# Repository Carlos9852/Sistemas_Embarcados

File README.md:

# Projeto_I
Projeto I da disciplina de Sistema Embarcados e Microcontroladores

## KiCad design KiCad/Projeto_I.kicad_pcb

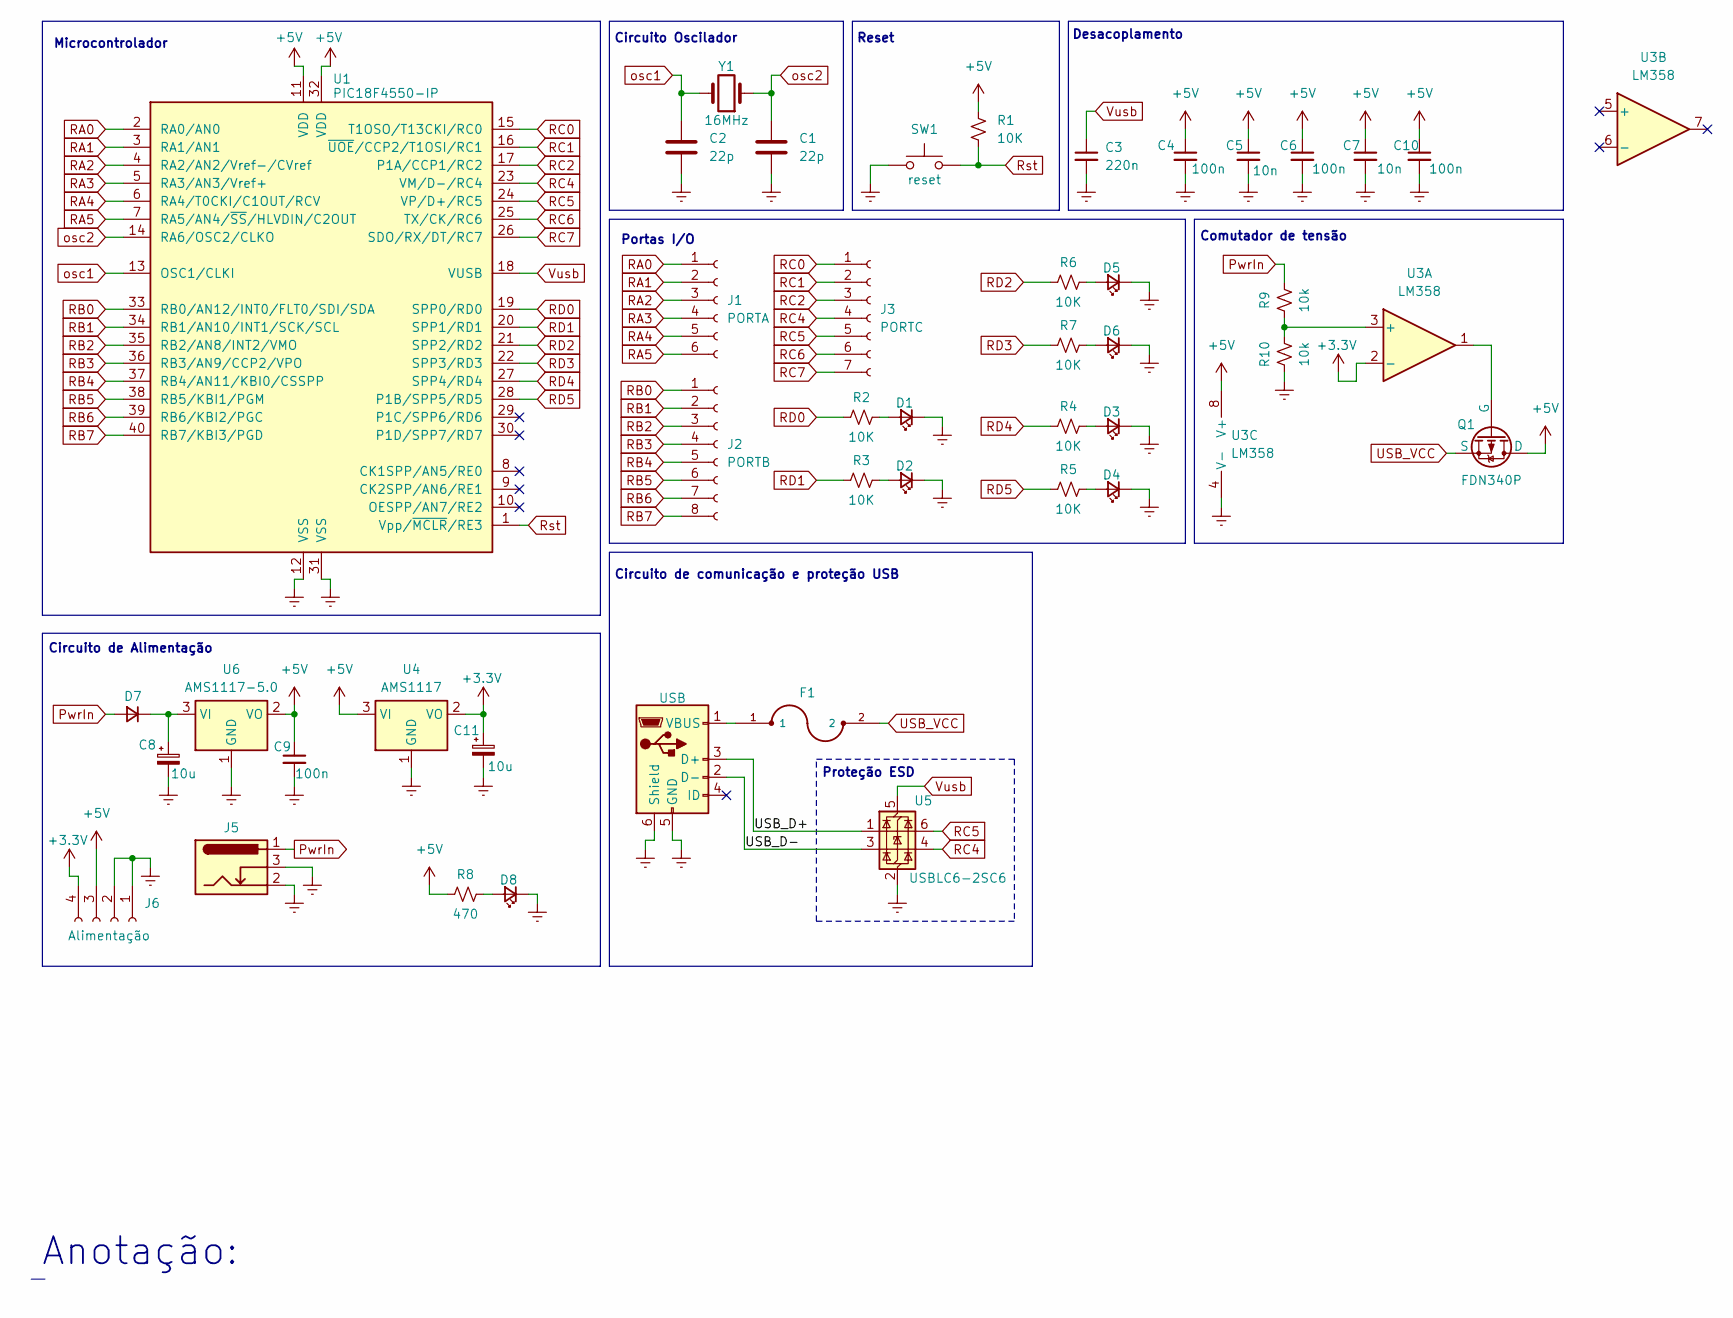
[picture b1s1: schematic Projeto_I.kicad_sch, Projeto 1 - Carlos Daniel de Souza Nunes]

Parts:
C1, C2: 22p; C_Disc_D5.0mm_W2.5mm_P2.50mm
C3: 220n; C_Rect_L7.0mm_W2.5mm_P5.00mm
C4, C6, C9, C10: 100n; C_Rect_L7.0mm_W2.5mm_P5.00mm
C5, C7: 10n; C_Rect_L7.0mm_W2.5mm_P5.00mm
C8, C11: 10u; CP_Radial_D5.0mm_P2.50mm
D1, D8: RD0; LED_D3.0mm
D2: RD1; LED_D3.0mm
D3: RD4; LED_D3.0mm
D4: RD5; LED_D3.0mm
D5: RD2; LED_D3.0mm
D6: RD3; LED_D3.0mm
D7: D_Small; D_DO-41_SOD81_P10.16mm_Horizontal
F1: MF-MSMF050-2; FUSM4632X85
J1: PORTA; PinSocket_1x06_P2.54mm_Vertical
J2: PORTB; PinSocket_1x08_P2.54mm_Vertical
J3: PORTC; PinSocket_1x07_P2.54mm_Vertical
J4: USB; USB_Micro-AB_Molex_47590-0001
J5: Barrel_Jack_Switch; BarrelJack_Horizontal
J6: Alimentação; PinSocket_1x04_P2.54mm_Vertical
Q1: FDN340P; SOT-23
R1, R2, R3, R4, R5, R6, R7: 10K; R_Axial_DIN0207_L6.3mm_D2.5mm_P7.62mm_Horizontal
R8: 470; R_Axial_DIN0207_L6.3mm_D2.5mm_P7.62mm_Horizontal
R9, R10: 10k; R_Axial_DIN0207_L6.3mm_D2.5mm_P7.62mm_Horizontal
SW1: reset; SW_TH_Tactile_Omron_B3F-10xx
U1: PIC18F4550-IP; DIP-40_W15.24mm
U3: LM358; DIP-8_W7.62mm
U4: AMS1117; SOT-223-3_TabPin2
U5: USBLC6-2SC6; SOT-23-6
U6: AMS1117-5.0; SOT-223-3_TabPin2
Y1: 16MHz; Crystal_HC49-U_Vertical

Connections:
+3.3V: C11.1, J6.4, U3.2 (-), U4.2 (VO)
+5V: C4.1, C5.1, C6.1, C7.1, C9.1, C10.1, J6.3, Q1.1 (D), R1.1, R8.1, U1.11 (VDD), U1.32 (VDD), U3.8 (V+), U4.3 (VI), U6.2 (VO); also elsewhere on the board
/USB_D+: J4.3 (D+), U5.1 (I/O1)
/USB_D-: J4.2 (D-), U5.3 (I/O2)
D+: J3.5, U1.24 (VP/D+/RC5), U5.6 (I/O1)
D-: J3.4, U1.23 (VM/D-/RC4), U5.4 (I/O2)
Earth: C1.2, C2.1, C3.2, C4.2, C5.2, C6.2, C7.2, C8.2, C9.2, C10.2, C11.2, D1.1 (K), D2.1 (K), D3.1 (K), D4.1 (K), D5.1 (K), D6.1 (K), D8.1 (K), J4.5 (GND), J4.6 (Shield), J5.2, J5.3, J6.1, J6.2, R10.1, SW1.1, U1.12 (VSS), U1.31 (VSS), U3.4 (V-), U4.1 (GND), U5.2 (GND), U6.1 (GND)
unnamed: D1.2 (A), R2.2
unnamed: D2.2 (A), R3.2
unnamed: D3.2 (A), R4.2
unnamed: D4.2 (A), R5.2
unnamed: D5.2 (A), R6.2
unnamed: D6.2 (A), R7.2
unnamed: C8.1, D7.1 (K), U6.3 (VI)
unnamed: D8.2 (A), R8.2
unnamed: F1.1, J4.1 (VBUS)
unnamed 16: Q1.2 (G), U3.1; also elsewhere on the board
unnamed: R9.1, R10.2, U3.3 (+)
PwrIn: D7.2 (A), J5.1, R9.2
RA0: J1.1, U1.2 (RA0/AN0)
RA1: J1.2, U1.3 (RA1/AN1)
RA2: J1.3, U1.4 (RA2/AN2/Vref-/CVref)
RA3: J1.4, U1.5 (RA3/AN3/Vref+)
RA4: J1.5, U1.6 (RA4/T0CKI/C1OUT/RCV)
RA5: J1.6, U1.7 (RA5/AN4/~SS/HLVDIN/C2OUT)
RB0: J2.1, U1.33 (RB0/AN12/INT0/FLT0/SDI/SDA)
RB1: J2.2, U1.34 (RB1/AN10/INT1/SCK/SCL)
RB2: J2.3, U1.35 (RB2/AN8/INT2/VMO)
RB3: J2.4, U1.36 (RB3/AN9/CCP2/VPO)
RB4: J2.5, U1.37 (RB4/AN11/KBI0/CSSPP)
RB5: J2.6, U1.38 (RB5/KBI1/PGM)
RB6: J2.7, U1.39 (RB6/KBI2/PGC)
RB7: J2.8, U1.40 (RB7/KBI3/PGD)
RC0: J3.1, U1.15 (T1OSO/T13CKI/RC0)
RC1: J3.2, U1.16 (~UOE/CCP2/T1OSI/RC1)
RC2: J3.3, U1.17 (P1A/CCP1/RC2)
RC6: J3.6, U1.25 (TX/CK/RC6)
RC7: J3.7, U1.26 (SDO/RX/DT/RC7)
RD0: R2.1, U1.19 (SPP0/RD0)
RD1: R3.1, U1.20 (SPP1/RD1)
RD2: R6.1, U1.21 (SPP2/RD2)
RD3: R7.1, U1.22 (SPP3/RD3)
RD4: R4.1, U1.27 (SPP4/RD4)
RD5: R5.1, U1.28 (P1B/SPP5/RD5)
Rst: R1.2, SW1.2, U1.1 (Vpp/~MCLR/RE3)
osc1: C2.2, U1.13 (OSC1/CLKI), Y1.2
osc2: C1.1, U1.14 (RA6/OSC2/CLKO), Y1.1

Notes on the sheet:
Portas I/O
Circuito de comunicação e proteção USB
Circuito Oscilador
Microcontrolador
Proteção ESD
Desacoplamento
Comutador de tensão
Anotação:
Reset
Circuito de Alimentação

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
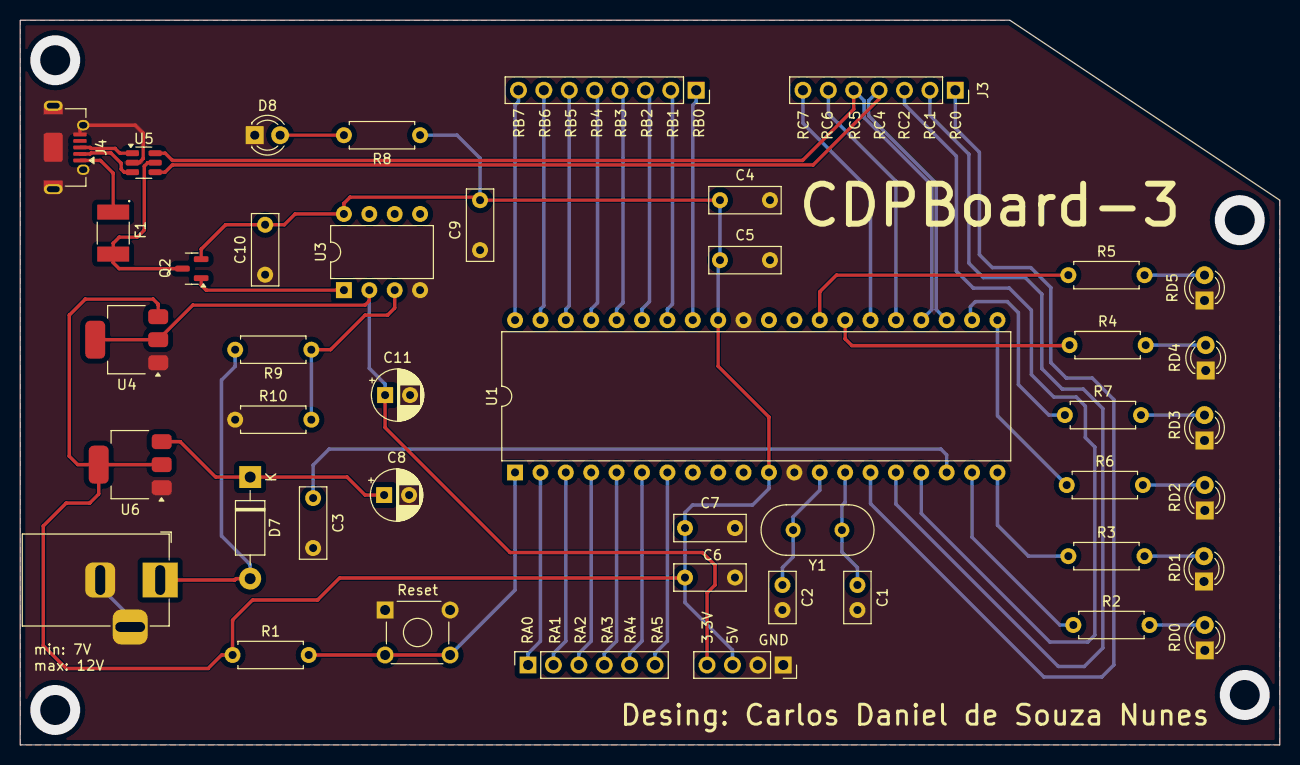
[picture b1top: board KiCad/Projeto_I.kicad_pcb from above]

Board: 2 copper layers, 126.0 x 72.5 mm, 44 parts (0 on the bottom side), 49 nets.

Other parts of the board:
Q2: FDN340P; SOT-23

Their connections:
+5V: Q2.2 (S); also elsewhere on the board
unnamed 16: Q2.1 (G); also elsewhere on the board

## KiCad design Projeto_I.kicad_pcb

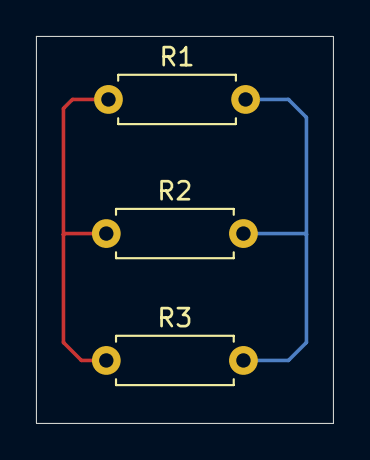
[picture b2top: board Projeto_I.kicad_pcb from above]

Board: 2 copper layers, 16.5 x 21.5 mm, 3 parts (0 on the bottom side), 2 nets.

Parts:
R1: 10k; R_Axial_DIN0207_L6.3mm_D2.5mm_P7.62mm_Horizontal
R2: 1k; R_Axial_DIN0207_L6.3mm_D2.5mm_P7.62mm_Horizontal
R3: 100; R_Axial_DIN0207_L6.3mm_D2.5mm_P7.62mm_Horizontal

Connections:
+5V: R1.1, R2.1, R3.1
Earth: R1.2, R2.2, R3.2

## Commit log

2025-03-22 Uploads de arquivos da primeira aula
2025-03-22 Integração das portas de entradas e saidas
2025-03-22 Inclusão dos módulos de alimentação e comutação
2025-03-29 Aula do dia 28/03
2025-04-05 AUla do dia 04/04/2025
2025-04-07 Inclusão do circuito de proteção ESD para o USB
2025-04-08 Atualização da PCB
2025-04-09 Atualização PCB
2025-04-09 Finalizção da PCB v1.1
2025-04-15 Atualização da PCB e conserto do esquemático do Transistor FDN340P
2025-05-10 Adicionado arquivos do Firmware com o programa de blink_led no RB4.
2025-05-10 Atualização no texto
2025-05-11 Simulando circuito de dois semáforos para a APS
2025-05-19 Carlos Daniel
2025-05-22 acrescentado o os arquivos dos displays de 7 segmentos
2025-05-31 atualização
2025-06-02 Atualização do software do relógio
